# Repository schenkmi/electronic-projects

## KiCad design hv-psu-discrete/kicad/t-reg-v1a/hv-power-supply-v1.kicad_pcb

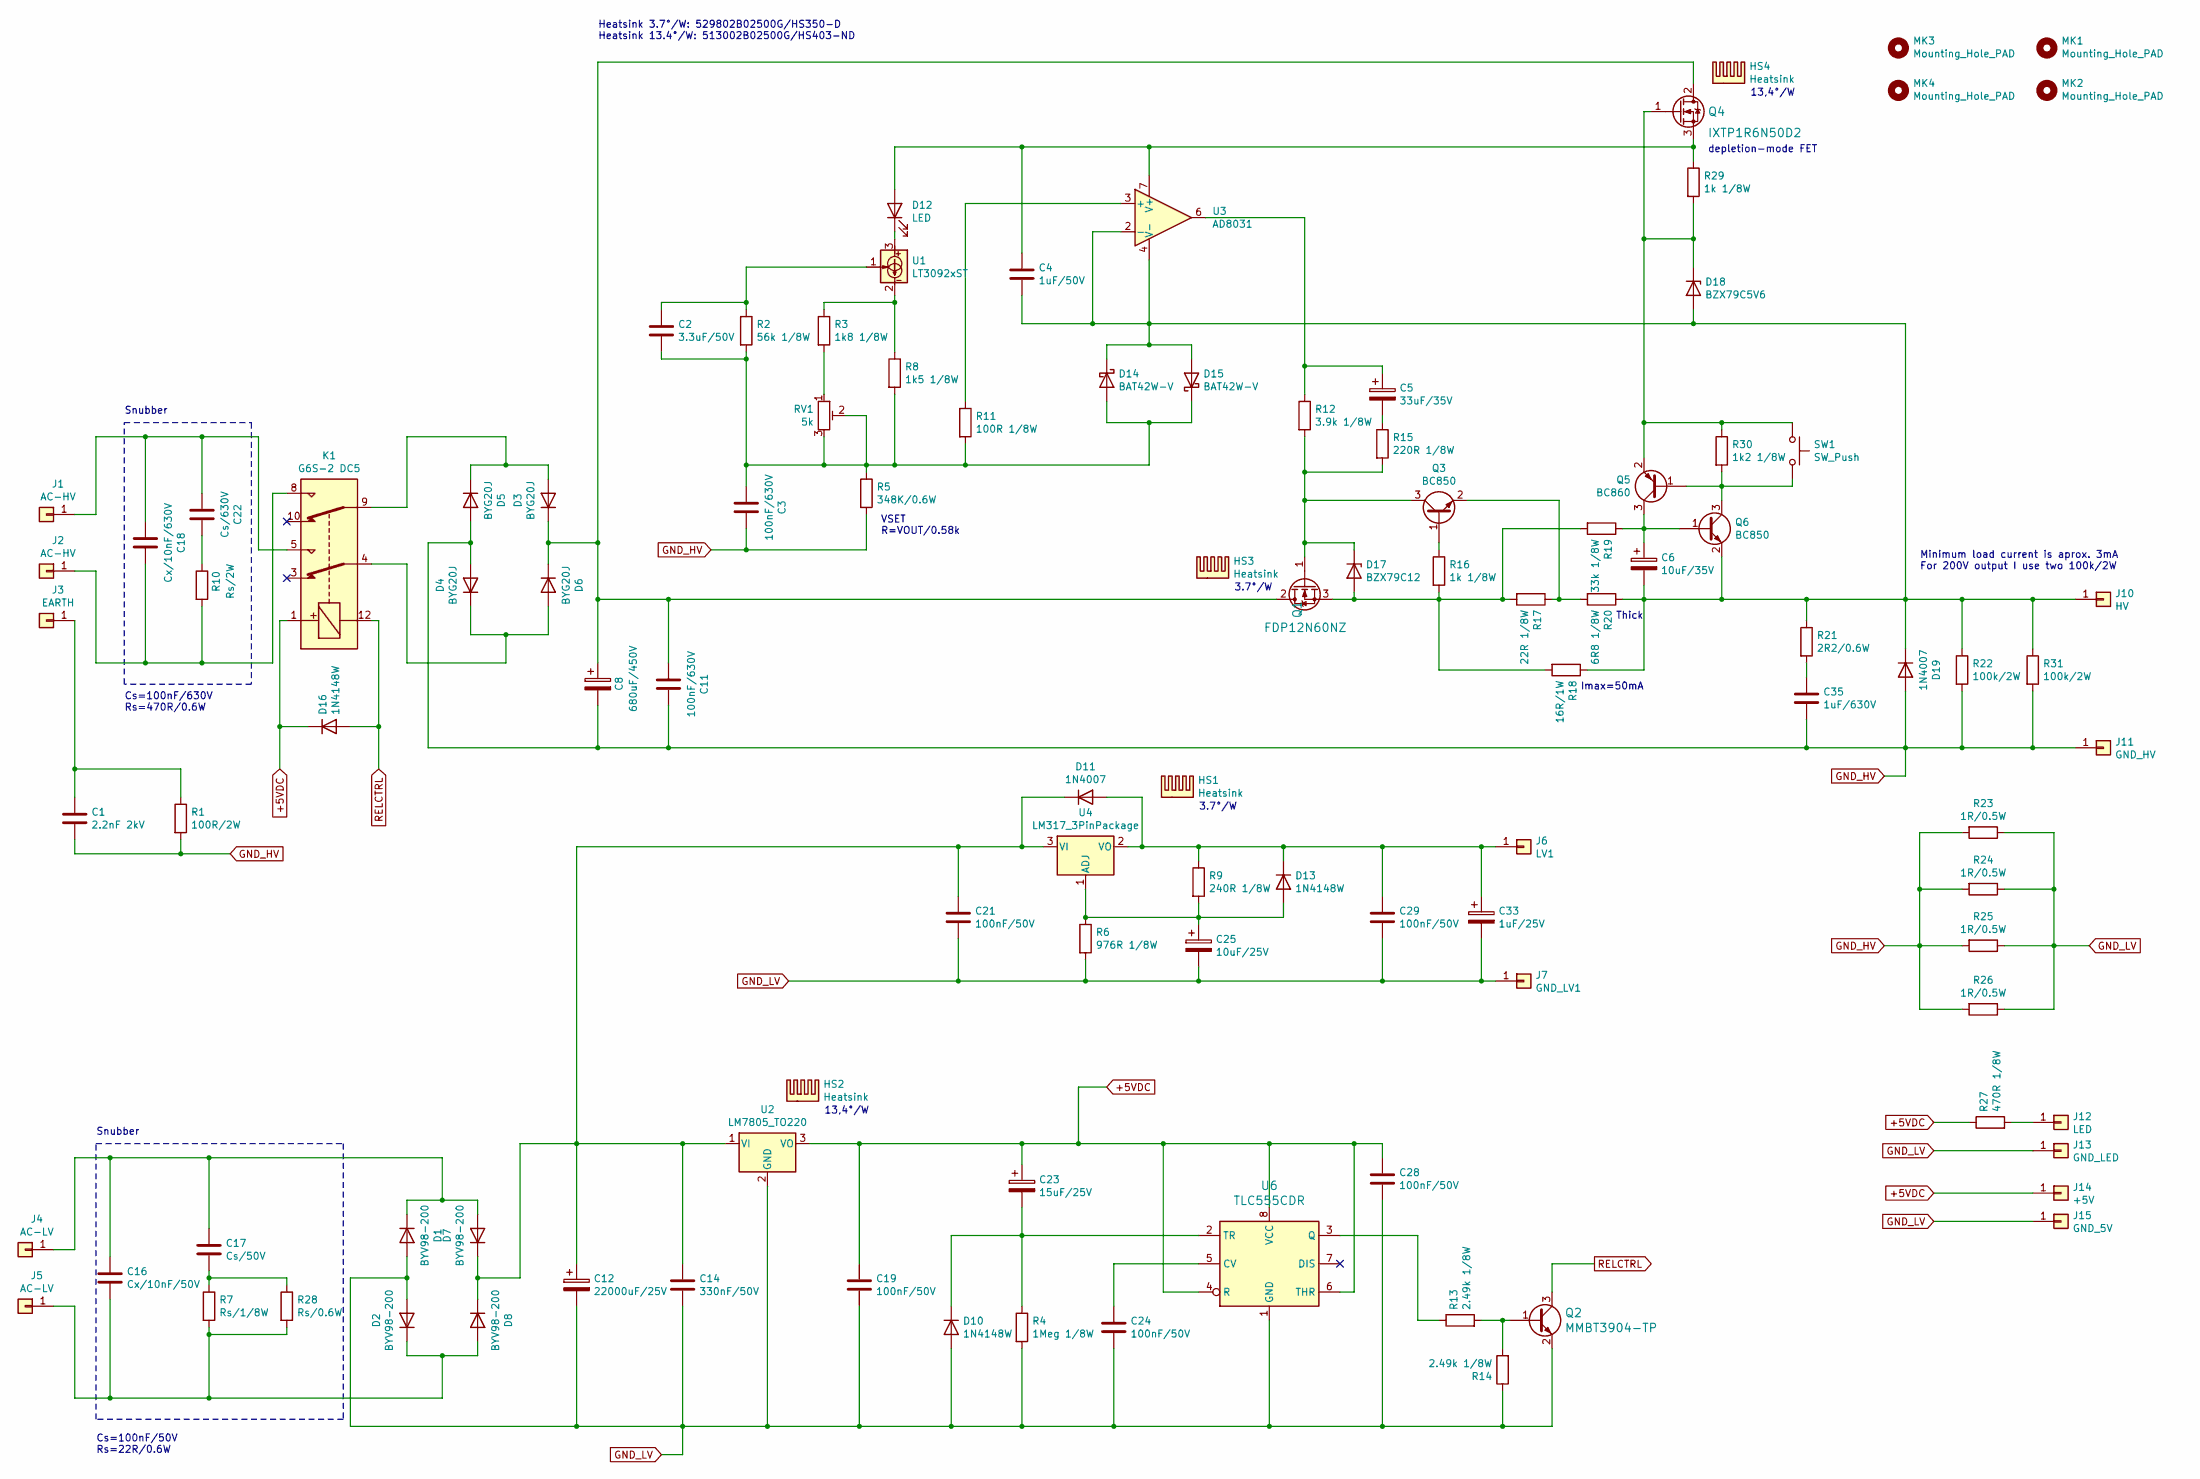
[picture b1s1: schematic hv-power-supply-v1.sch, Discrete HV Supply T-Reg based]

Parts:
C1: 2.2nF 2kV; C_Rect_L18.0mm_W5.0mm_P15.00mm_FKS3_FKP3
C2: 3.3uF/50V; C_1210_3225Metric_Pad1.33x2.70mm_HandSolder
C3, C11: 100nF/630V; C_Rect_L18.0mm_W5.0mm_P15.00mm_FKS3_FKP3
C4: 1uF/50V; C_0805_2012Metric_Pad1.18x1.45mm_HandSolder
C5: 33uF/35V; CP_Radial_D5.0mm_P2.00mm
C6: 10uF/35V; CP_Radial_D5.0mm_P2.00mm
C8: 680uF/450V; CP_Radial_D35.0mm_P10.00mm_SnapIn
C12: 22000uF/25V; CP_Radial_D35.0mm_P10.00mm_SnapIn
C14: 330nF/50V; C_0805_2012Metric_Pad1.18x1.45mm_HandSolder
C16: Cx/10nF/50V; C_0805_2012Metric_Pad1.18x1.45mm_HandSolder
C17: Cs/50V; C_0805_2012Metric_Pad1.18x1.45mm_HandSolder
C18: Cx/10nF/630V; C_Rect_L13.0mm_W4.0mm_P10.00mm_FKS3_FKP3_MKS4
C19, C21, C24, C28, C29: 100nF/50V; C_0805_2012Metric_Pad1.18x1.45mm_HandSolder
C22: Cs/630V; C_Rect_L18.0mm_W5.0mm_P15.00mm_FKS3_FKP3
C23: 15uF/25V; CP_EIA-7343-31_Kemet-D_Pad2.25x2.55mm_HandSolder
C25: 10uF/25V; CP_Radial_D5.0mm_P2.00mm
C33: 1uF/25V; CP_Radial_D5.0mm_P2.00mm
C35: 1uF/630V; C_Rect_L26.5mm_W11.5mm_P22.50mm_MKS4
D1, D2, D7, D8: BYV98-200; SOD64-10
D3, D4, D5, D6: BYG20J; D_SMA_Handsoldering
D10, D13, D16: 1N4148W; D_SOD-123
D11, D19: 1N4007; D_SMA_Handsoldering
D12: LED; LED_D3.0mm
D14, D15: BAT42W-V; D_SOD-123
D17: BZX79C12; D_DO-35_SOD27_P7.62mm_Horizontal
D18: BZX79C5V6; D_DO-35_SOD27_P7.62mm_Horizontal
HS1, HS3: Heatsink; Heatsink_Fischer_SK129-STS_42x25mm_2xDrill2.5mm
HS2, HS4: Heatsink; Heatsink_Fischer_SK104-STC-STIC_35x13mm_2xDrill2.5mm
J1, J2: AC-HV; Pin_D1.3mm_L11.0mm
J3: EARTH; Pin_D1.3mm_L11.0mm
J4, J5: AC-LV; Pin_D1.3mm_L11.0mm
J6: LV1; Pin_D1.3mm_L11.0mm
J7: GND_LV1; Pin_D1.3mm_L11.0mm
J10: HV; Pin_D1.3mm_L11.0mm
J11: GND_HV; Pin_D1.3mm_L11.0mm
J12: LED; Pin_D1.0mm_L10.0mm
J13: GND_LED; Pin_D1.0mm_L10.0mm
J14: +5V; Pin_D1.0mm_L10.0mm
J15: GND_5V; Pin_D1.0mm_L10.0mm
K1: G6S-2 DC5; Relay_DPDT_Omron_G6S-2
MK1, MK2, MK3, MK4: Mounting_Hole_PAD; MountingHole_3.2mm_M3
Q1: FDP12N60NZ; TO-220-3_Vertical; MPN IRF510PBF; Digi-Key_PN IRF510PBF-ND
Q2: MMBT3904-TP; SOT-23; MPN MMBT3904-TP; Digi-Key_PN MMBT3904TPMSCT-ND
Q3, Q6: BC850; SOT-23
Q4: IXTP1R6N50D2; TO-220-3_Vertical; MPN IRF510PBF; Digi-Key_PN IRF510PBF-ND
Q5: BC860; SOT-23
R1: 100R/2W; R_Axial_DIN0414_L11.9mm_D4.5mm_P15.24mm_Horizontal
R2: 56k 1/8W; R_0805_2012Metric_Pad1.20x1.40mm_HandSolder
R3: 1k8 1/8W; R_0805_2012Metric_Pad1.20x1.40mm_HandSolder
R4: 1Meg 1/8W; R_0805_2012Metric_Pad1.20x1.40mm_HandSolder
R5: 348K/0.6W; R_Axial_DIN0207_L6.3mm_D2.5mm_P10.16mm_Horizontal
R6: 976R 1/8W; R_0805_2012Metric_Pad1.20x1.40mm_HandSolder
R7: Rs/1/8W; R_0805_2012Metric_Pad1.20x1.40mm_HandSolder
R8: 1k5 1/8W; R_0805_2012Metric_Pad1.20x1.40mm_HandSolder
R9: 240R 1/8W; R_0805_2012Metric_Pad1.20x1.40mm_HandSolder
R10: Rs/2W; R_Axial_DIN0414_L11.9mm_D4.5mm_P15.24mm_Horizontal
R11: 100R 1/8W; R_0805_2012Metric_Pad1.20x1.40mm_HandSolder
R12: 3.9k 1/8W; R_0805_2012Metric_Pad1.20x1.40mm_HandSolder
R13, R14: 2.49k 1/8W; R_0805_2012Metric_Pad1.20x1.40mm_HandSolder
R15: 220R 1/8W; R_0805_2012Metric_Pad1.20x1.40mm_HandSolder
R16, R29: 1k 1/8W; R_0805_2012Metric_Pad1.20x1.40mm_HandSolder
R17: 22R 1/8W; R_0805_2012Metric_Pad1.20x1.40mm_HandSolder
R18: 16R/1W; R_Axial_DIN0207_L6.3mm_D2.5mm_P10.16mm_Horizontal
R19: 33k 1/8W; R_0805_2012Metric_Pad1.20x1.40mm_HandSolder
R20: 6R8 1/8W; R_0805_2012Metric_Pad1.20x1.40mm_HandSolder
R21: 2R2/0.6W; R_Axial_DIN0207_L6.3mm_D2.5mm_P10.16mm_Horizontal
R22, R31: 100k/2W; R_Axial_DIN0414_L11.9mm_D4.5mm_P15.24mm_Horizontal
R23, R24, R25, R26: 1R/0.5W; R_0805_2012Metric_Pad1.20x1.40mm_HandSolder
R27: 470R 1/8W; R_0805_2012Metric_Pad1.20x1.40mm_HandSolder
R28: Rs/0.6W; R_Axial_DIN0207_L6.3mm_D2.5mm_P10.16mm_Horizontal
R30: 1k2 1/8W; R_0805_2012Metric_Pad1.20x1.40mm_HandSolder
RV1: 5k; Potentiometer_Bourns_3296W_Vertical
SW1: SW_Push; SW_SPST_B3U-1000P
U1: LT3092xST; SOT-223-3_TabPin2
U2: LM7805_TO220; TO-220-3_Vertical
U3: AD8031; SOIC-8_3.9x4.9mm_P1.27mm
U4: LM317_3PinPackage; TO-220-3_Vertical
U6: TLC555CDR; SOIC-8_3.9x4.9mm_P1.27mm; MPN TLC555CDR; Digi-Key_PN 296-1336-1-ND

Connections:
+5VDC: C19.1, C23.1, C28.1, D16.1 (K), J14.1, K1.1, R27.1, U2.3 (VO), U6.4 (R), U6.6 (THR), U6.8 (VCC)
GND_HV: C1.2, C3.1, C8.2, C11.1, C35.2, D4.2 (A), D5.2 (A), D19.2 (A), J11.1, R1.2, R5.2, R22.2, R23.2, R24.2, R25.2, R26.2, R31.2
GND_LV: C12.2, C14.2, C19.2, C21.2, C24.2, C25.2, C28.2, C29.2, C33.2, D1.2 (A), D2.2 (A), D10.2 (A), J7.1, J13.1, J15.1, Q2.2 (E), R4.2, R6.2, R14.1, R23.1, R24.1, R25.1, R26.1, U2.2 (GND), U6.1 (GND)
unnamed: C1.1, J3.1, R1.1
unnamed: C2.1, R2.1, U1.1
unnamed: C2.2, C3.2, D14.2 (A), D15.1 (K), R2.2, R5.1, R8.2, R11.2, RV1.2, RV1.3
unnamed: C4.1, D12.2 (A), Q4.3 (S), R29.1, U3.7 (V+)
unnamed: C4.2, C6.2, D14.1 (K), D15.2 (A), D18.2 (A), D19.1 (K), J10.1, Q6.2 (E), R18.1, R20.1, R21.1, R22.1, R31.1, U3.2 (-), U3.4 (V-)
unnamed: C5.1, R12.1, U3.6
unnamed: C5.2, R15.1
unnamed: C6.1, Q5.3 (C), Q6.1 (B), R19.1
unnamed: C8.1, C11.2, D3.1 (K), D6.1 (K), Q1.2 (D), Q4.2 (D)
unnamed: C12.1, C14.1, C21.1, D7.1 (K), D8.1 (K), D11.1 (K), U2.1 (VI), U4.3 (VI)
unnamed: C16.1, C17.1, D1.1 (K), D7.2 (A), J4.1
unnamed: C16.2, D2.1 (K), D8.2 (A), J5.1, R7.2, R28.2
unnamed: C17.2, R7.1, R28.1
unnamed: C18.1, J2.1, K1.8, R10.2
unnamed: C18.2, C22.2, J1.1, K1.5
unnamed: C22.1, R10.1
unnamed: C23.2, D10.1 (K), R4.1, U6.2 (TR)
unnamed: C24.1, U6.5 (CV)
unnamed: C25.1, D13.2 (A), R6.1, R9.2, U4.1 (ADJ)
unnamed: C29.1, C33.1, D11.2 (A), D13.1 (K), J6.1, R9.1, U4.2 (VO)
unnamed: C35.1, R21.2
unnamed: D3.2 (A), D5.1 (K), K1.9
unnamed: D4.1 (K), D6.2 (A), K1.4
unnamed: D12.1 (K), U1.3
unnamed: D17.1 (K), Q1.1 (G), Q3.3 (C), R12.2, R15.2
unnamed: D17.2 (A), Q1.3 (S), R16.2, R17.2, R18.2, R19.2
unnamed: D18.1 (K), Q4.1 (G), Q5.2 (E), R29.2, R30.1, SW1.1
unnamed: J12.1, R27.2
unnamed: Q2.1 (B), R13.2, R14.2
unnamed: Q3.1 (B), R16.1
unnamed: Q3.2 (E), R17.1, R20.2
unnamed: Q5.1 (B), Q6.3 (C), R30.2, SW1.2
unnamed: R3.1, R8.1, U1.2
unnamed: R3.2, RV1.1
unnamed: R11.1, U3.3 (+)
unnamed: R13.1, U6.3 (Q)
RELCTRL: D16.2 (A), K1.12, Q2.3 (C)

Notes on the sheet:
Snubber
VSET R=VOUT/0.58k
Imax=50mA
Cs=100nF/630V Rs=470R/0.6W
Cs=100nF/50V Rs=22R/0.6W
3.7°/W
13,4°/W
Thick
depletion-mode FET
Minimum load current is aprox. 3mA For 200V output I use two 100k/2W
Heatsink 3.7°/W: 529802B02500G/HS350-D Heatsink 13.4°/W: 513002B02500G/HS403-ND

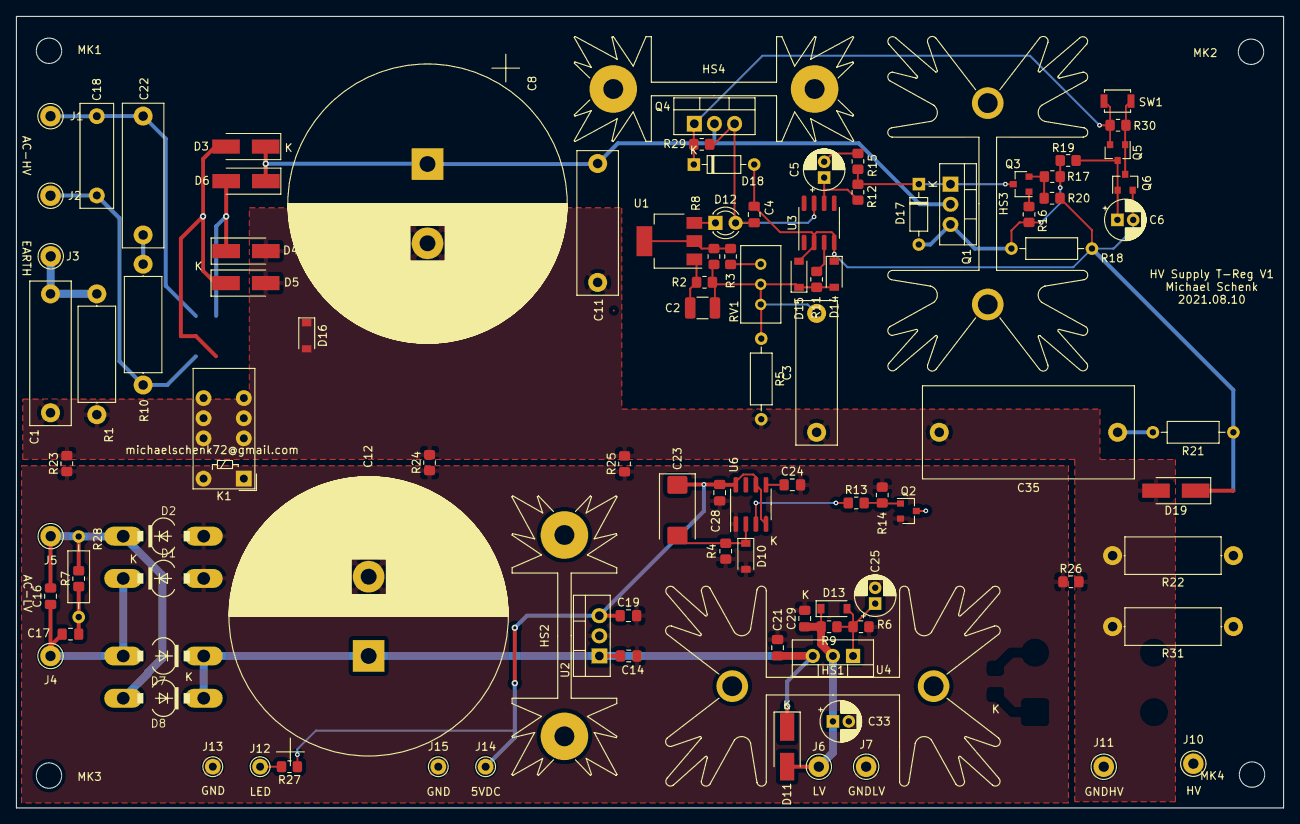
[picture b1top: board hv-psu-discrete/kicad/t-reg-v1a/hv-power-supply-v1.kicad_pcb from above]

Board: 2 copper layers, 159.9 x 99.9 mm, 107 parts (0 on the bottom side), 40 nets.

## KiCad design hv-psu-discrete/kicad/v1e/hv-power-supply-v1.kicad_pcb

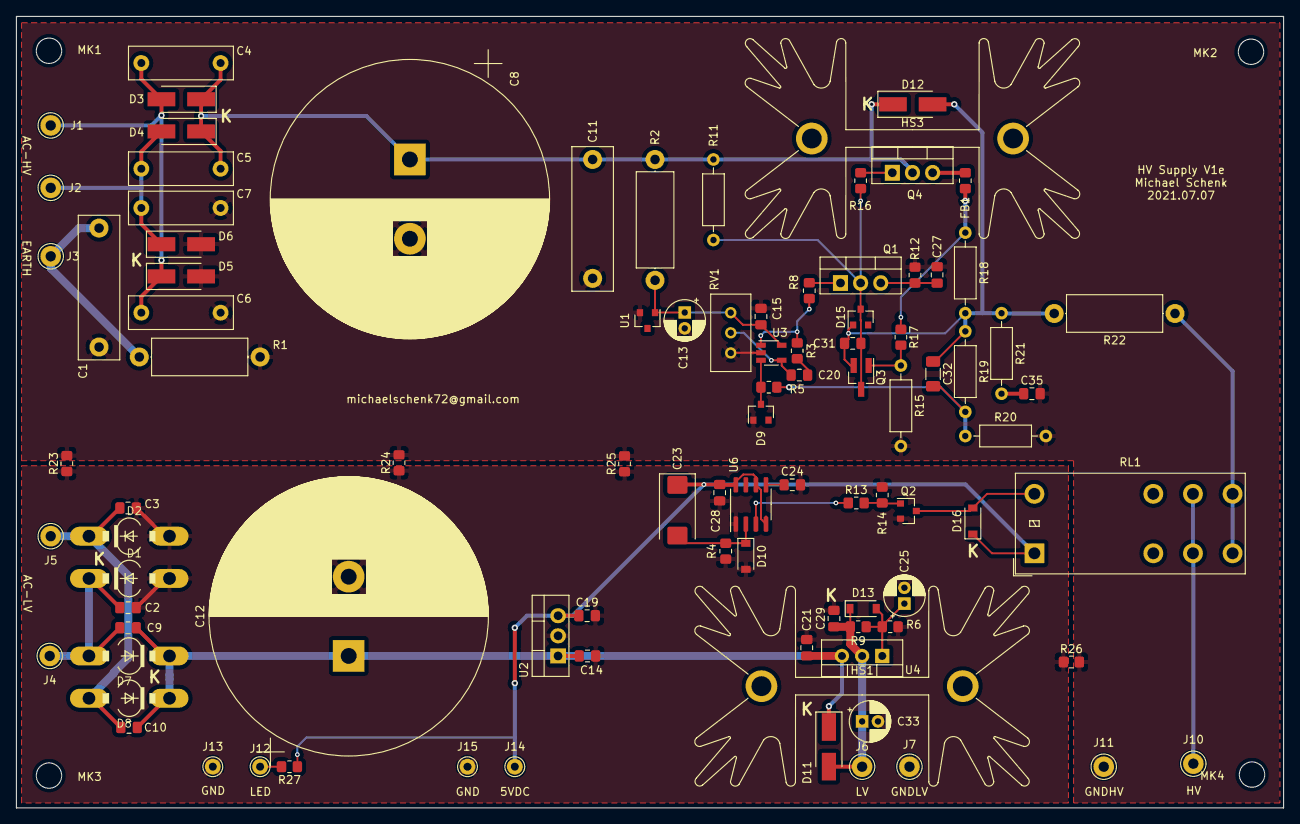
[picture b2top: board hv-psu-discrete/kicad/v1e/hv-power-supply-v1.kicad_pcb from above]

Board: 2 copper layers, 159.9 x 99.9 mm, 99 parts (0 on the bottom side), 35 nets.

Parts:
C1: 2.2nF 2kV; C_Rect_L18.0mm_W5.0mm_P15.00mm_FKS3_FKP3
C2, C3, C9, C10, C20: 10nF/50V; C_0805_2012Metric_Pad1.18x1.45mm_HandSolder
C4, C5, C6, C7: 10nF/630V; C_Rect_L13.0mm_W4.0mm_P10.00mm_FKS3_FKP3_MKS4
C8: 680uF/450V; CP_Radial_D35.0mm_P10.00mm_SnapIn
C11: 100nF/630V; C_Rect_L18.0mm_W5.0mm_P15.00mm_FKS3_FKP3
C12: 22000uF/25V; CP_Radial_D35.0mm_P10.00mm_SnapIn
C13, C25: 10uF/25V; CP_Radial_D5.0mm_P2.00mm
C14: 330nF/50V; C_0805_2012Metric_Pad1.18x1.45mm_HandSolder
C15, C19, C21, C24, C28, C29: 100nF/50V; C_0805_2012Metric_Pad1.18x1.45mm_HandSolder
C23: 15uF/25V; CP_EIA-7343-31_Kemet-D_Pad2.25x2.55mm_HandSolder
C27: 0pF/50V; C_0805_2012Metric_Pad1.18x1.45mm_HandSolder
C31: 1nF/50V; C_0805_2012Metric_Pad1.18x1.45mm_HandSolder
C32: 10pF/500V; C_1206_3216Metric_Pad1.33x1.80mm_HandSolder
C33: 1uF/25V; CP_Radial_D5.0mm_P2.00mm
C35: 470pF/500V; C_0805_2012Metric_Pad1.18x1.45mm_HandSolder
D1, D2, D7, D8: BYV98-200; SOD64-10
D3, D4, D5, D6: BYG20J; D_SMA_Handsoldering
D9: BAT54C; SOT-23
D10, D13, D16: 1N4148W; D_SOD-123
D11, D12: 1N4007; D_SMA_Handsoldering
D15: BZX84C15; D_SOT-23_ANK
FB1: 600R@100MHz; R_0805_2012Metric_Pad1.20x1.40mm_HandSolder
HS1, HS3: Heatsink; Heatsink_Fischer_SK129-STS_42x25mm_2xDrill2.5mm
J1, J2: AC-HV; Pin_D1.3mm_L11.0mm
J3: EARTH; Pin_D1.3mm_L11.0mm
J4, J5: AC-LV; Pin_D1.3mm_L11.0mm
J6: LV1; Pin_D1.3mm_L11.0mm
J7: GND_LV1; Pin_D1.3mm_L11.0mm
J10: HV; Pin_D1.3mm_L11.0mm
J11: GND_HV; Pin_D1.3mm_L11.0mm
J12: LED; Pin_D1.0mm_L10.0mm
J13: GND_LED; Pin_D1.0mm_L10.0mm
J14: +5V; Pin_D1.0mm_L10.0mm
J15: GND_5V; Pin_D1.0mm_L10.0mm
MK1, MK2, MK3, MK4: Mounting_Hole_PAD; MountingHole_3.2mm_M3
Q1, Q4: IRF840; TO-220-3_Vertical
Q2: MMBT3904-TP; SOT-23
Q3: MMBT3904-TP; SOT-23_Handsoldering
R1: 100R/2W; R_Axial_DIN0414_L11.9mm_D4.5mm_P15.24mm_Horizontal
R2: 100k/2W; R_Axial_DIN0414_L11.9mm_D4.5mm_P15.24mm_Horizontal
R3: 0R 1/8W; R_0805_2012Metric_Pad1.20x1.40mm_HandSolder
R4: 1Meg 1/8W; R_0805_2012Metric_Pad1.20x1.40mm_HandSolder
R5: 10K 1/8W; R_0805_2012Metric_Pad1.20x1.40mm_HandSolder
R6: 976R 1/8W; R_0805_2012Metric_Pad1.20x1.40mm_HandSolder
R8, R16: 100R 1/8W; R_0805_2012Metric_Pad1.20x1.40mm_HandSolder
R9: 240R 1/8W; R_0805_2012Metric_Pad1.20x1.40mm_HandSolder
R11: 470k/0.6W; R_Axial_DIN0207_L6.3mm_D2.5mm_P10.16mm_Horizontal
R12: 2.7k 1/8W; R_0805_2012Metric_Pad1.20x1.40mm_HandSolder
R13, R14: 2.49k 1/8W; R_0805_2012Metric_Pad1.20x1.40mm_HandSolder
R15: 200k/0.6W; R_Axial_DIN0207_L6.3mm_D2.5mm_P10.16mm_Horizontal
R17: 4.99k,1/8W; R_0805_2012Metric_Pad1.20x1.40mm_HandSolder
R18: 12R/0.6W; R_Axial_DIN0207_L6.3mm_D2.5mm_P10.16mm_Horizontal
R19: 402K/0.6W; R_Axial_DIN0207_L6.3mm_D2.5mm_P10.16mm_Horizontal
R20: 10K/0.6W; R_Axial_DIN0207_L6.3mm_D2.5mm_P10.16mm_Horizontal
R21: 750/0.6W; R_Axial_DIN0207_L6.3mm_D2.5mm_P10.16mm_Horizontal
R22: 330R2W; R_Axial_DIN0414_L11.9mm_D4.5mm_P15.24mm_Horizontal
R23, R24, R25, R26: 1R/0.5W; R_0805_2012Metric_Pad1.20x1.40mm_HandSolder
R27: 470R 1/8W; R_0805_2012Metric_Pad1.20x1.40mm_HandSolder
RL1: G2RL-2-DC5; Relay_DPDT_Omron_G2RL
RV1: 100k; Potentiometer_Bourns_3296W_Vertical
U1: LM4040DBZ-10; SOT-23
U2: LM7805_TO220; TO-220-3_Vertical
U3: OPA188xxDBV; TSOT-23-5
U4: LM317_3PinPackage; TO-220-3_Vertical
U6: TLC555CDR; SOIC-8_3.9x4.9mm_P1.27mm

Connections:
+5VDC: C19.1, C23.1, C28.1, D16.1, J14.1, R27.1, RL1.1, U2.3, U6.4, U6.6, U6.8
GND_HV: C1.2, C6.1, C7.1, C8.2, C11.1, C13.2, C15.2, C27.2, C35.2, D5.2, D6.2, D9.1, J11.1, R1.2, R12.1, R15.2, R20.2, R23.2, R24.2, R25.2, R26.2, RV1.3, U1.2, U3.2
GND_LV: C2.2, C3.1, C12.2, C14.2, C19.2, C21.2, C24.2, C25.2, C28.2, C29.2, C33.2, D1.2, D2.2, D10.2, J7.1, J13.1, J15.1, Q2.2, R4.2, R6.2, R14.1, R23.1, R24.1, R25.1, R26.1, U2.2, U6.1
HV: R22.1, RL1.4, RL1.5
unnamed: C1.1, J3.1, R1.1
unnamed: C2.1, C9.1, D1.1, D7.2, J4.1
unnamed: C4.2, C6.2, D3.2, D5.1, J1.1
unnamed: C5.2, C7.2, D4.2, D6.1, J2.1
unnamed: C9.2, C10.1, C12.1, C14.1, C21.1, D7.1, D8.1, D11.1, U2.1, U4.3
unnamed: C3.2, C10.2, D2.1, D8.2, J5.1
unnamed: C4.1, C5.1, C8.1, C11.2, D3.1, D4.1, D12.1, Q4.2, R2.1, R11.1
unnamed: C13.1, C15.1, R2.2, RV1.1, U1.1, U3.5
unnamed: C20.1, RV1.2, U3.4
unnamed: C20.2, R3.1
unnamed: C23.2, D10.1, R4.1, U6.2
unnamed: C24.1, U6.5
unnamed: C25.1, D13.2, R6.1, R9.2, U4.1
unnamed: C27.1, Q1.3, R12.2
unnamed: C29.1, C33.1, D11.2, D13.1, J6.1, R9.1, U4.2
unnamed: C31.1, D15.1, Q1.2, Q3.3, R11.2, R16.1
unnamed: C31.2, C32.1, D12.2, D15.2, Q3.2, R18.2, R19.1, R21.1, R22.2
unnamed: C32.2, R5.1, R19.2, R20.1
unnamed: C35.1, R21.2
unnamed: D9.3, R5.2, U3.3
unnamed: D16.2, Q2.3, RL1.8
unnamed: FB1.1, Q4.3
unnamed: FB1.2, R17.1, R18.1
unnamed: J10.1, RL1.3, RL1.6
unnamed: J12.1, R27.2
unnamed: Q1.1, R8.1
unnamed: Q2.1, R13.2, R14.2
unnamed: Q3.1, R15.1, R17.2
unnamed: Q4.1, R16.2
unnamed: R3.2, R8.2, U3.1
unnamed: R13.1, U6.3
